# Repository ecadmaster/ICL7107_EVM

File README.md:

# ICL7107 Evaluation Module (EVM)

Este repositorio contiene el diseño de hardware de una tarjeta de evaluación para el ICL7107, un convertidor analógico-digital (ADC) de 3.5 dígitos diseñado para controlar displays LED. Este proyecto se desarrolla como material de práctica para la asignatura Laboratorio de Electrónica II de la Universidad de Los Andes (ULA).

## Descripción del Proyecto

El ICL7107 es un circuito integrado ampliamente utilizado en la instrumentación electrónica, específicamente en la construcción de voltímetros y multímetros digitales. Esta placa permite a los estudiantes y entusiastas experimentar con el acondicionamiento de señales y la visualización de datos sin necesidad de realizar el cableado complejo en protoboard.

## Características Técnicas

- Conversor: ICL7107 (ADC Dual-Slope).
- Visualización: 3.5 dígitos para displays de siete segmentos (ánodo común).
- Alimentación: $$+5VDC$$ vía microUSB, internamente contiene circuito inversor para el $$-5VDC$$.
- Ajustes: Potenciómetro de precisión para calibración de voltaje de referencia.
- Software de Diseño: [KiCad EDA](https://www.kicad.org/)  9.0 (o superior).

## Esquema del Circuito

A continuación, se presenta el diagrama esquemático del sistema:

## Lista de Materiales (BOM)

Para ensamblar este módulo, se requieren los siguientes componentes:

| Cantidad | Referencia | Descripción |
| :----------- | :-------------- | :------------- |
| 1	| C1 | Capacitor Electrolítico 47uF/16V |
| 5	| C2-6 | Capacitor Electrolítico 1uF/25V |
| 1	| C7 | Capacitor Cerámico 0.47uF |
| 1	| C8 | Capacitor Cerámico 0.22uF |
| 7	| C9-15 | Capacitor Cerámico 0.1uF |
| 1	| C16 | Capacitor Cerámico 0.047uF |
| 1	| C17 | Capacitor Cerámico 100pF |
| 4	| D1-4 | Display 7 segmentos, ánodo común |
| 1	| D5 | Diodo Zener 2.4V |
| 1	| J1 | Bornera 2 pines |
| 1	| JP1-6 | 1x02 Pin header con jumpers |
| 1	| P1 | Conector microUSB |
| 1	| R1 | Resistencia 1/4W 1 M ohm |
| 1	| R2 | Resistencia 1/4W 470k ohm |
| 1	| R3 | Resistencia 1/4W 100k ohm |
| 1	| R4 | Resistencia 1/4W 47k ohm |
| 1	| R5 | Resistencia 1/4W 10k ohm |
| 4	| R6-9 | Resistencia 1/4W 330 ohm |
| 1	| RV1 | Potenciómetro Trimmer 1k ohm |
| 1	| SW1 | Pulsador 6mm |
| 3	| SW2-4 | Switch, CuK OS102011MA1QN1 o similar |
| 1	| TP1-2 | Punta de prueba, Keystone 5010 o similar |
| 1	| U1 | Base de 40 pines + ICL7107 |
| 1	| U2 | Base de 16 pines + MAX232 |
| 1	| U3 | Regulador LM7905 |

Nota 1: La lista completa detallada se encuentra en el archivo ICL7107_EVM_BOM.csv

Nota 2: Se recomienda colocar 8x sockets de 1x05 pines hembra para la instalación de los display 7-segmento, de modo que pueda removerlos fácilmente de ser necesario.

## Instalación y Uso

Clona el repositorio:

```git clone https://github.com/ecadmaster/ICL7107_EVM.git```

Abre el archivo .kicad_pro con KiCad para revisar el PCB o generar los archivos Gerber para fabricación.

Consulta la datasheet para entender los límites operativos del integrado.

## Contribuciones y Licencia
Este proyecto está bajo la licencia MIT. Las sugerencias de mejora para el entorno académico de la Escuela de Ingeniería Eléctrica son bienvenidas.

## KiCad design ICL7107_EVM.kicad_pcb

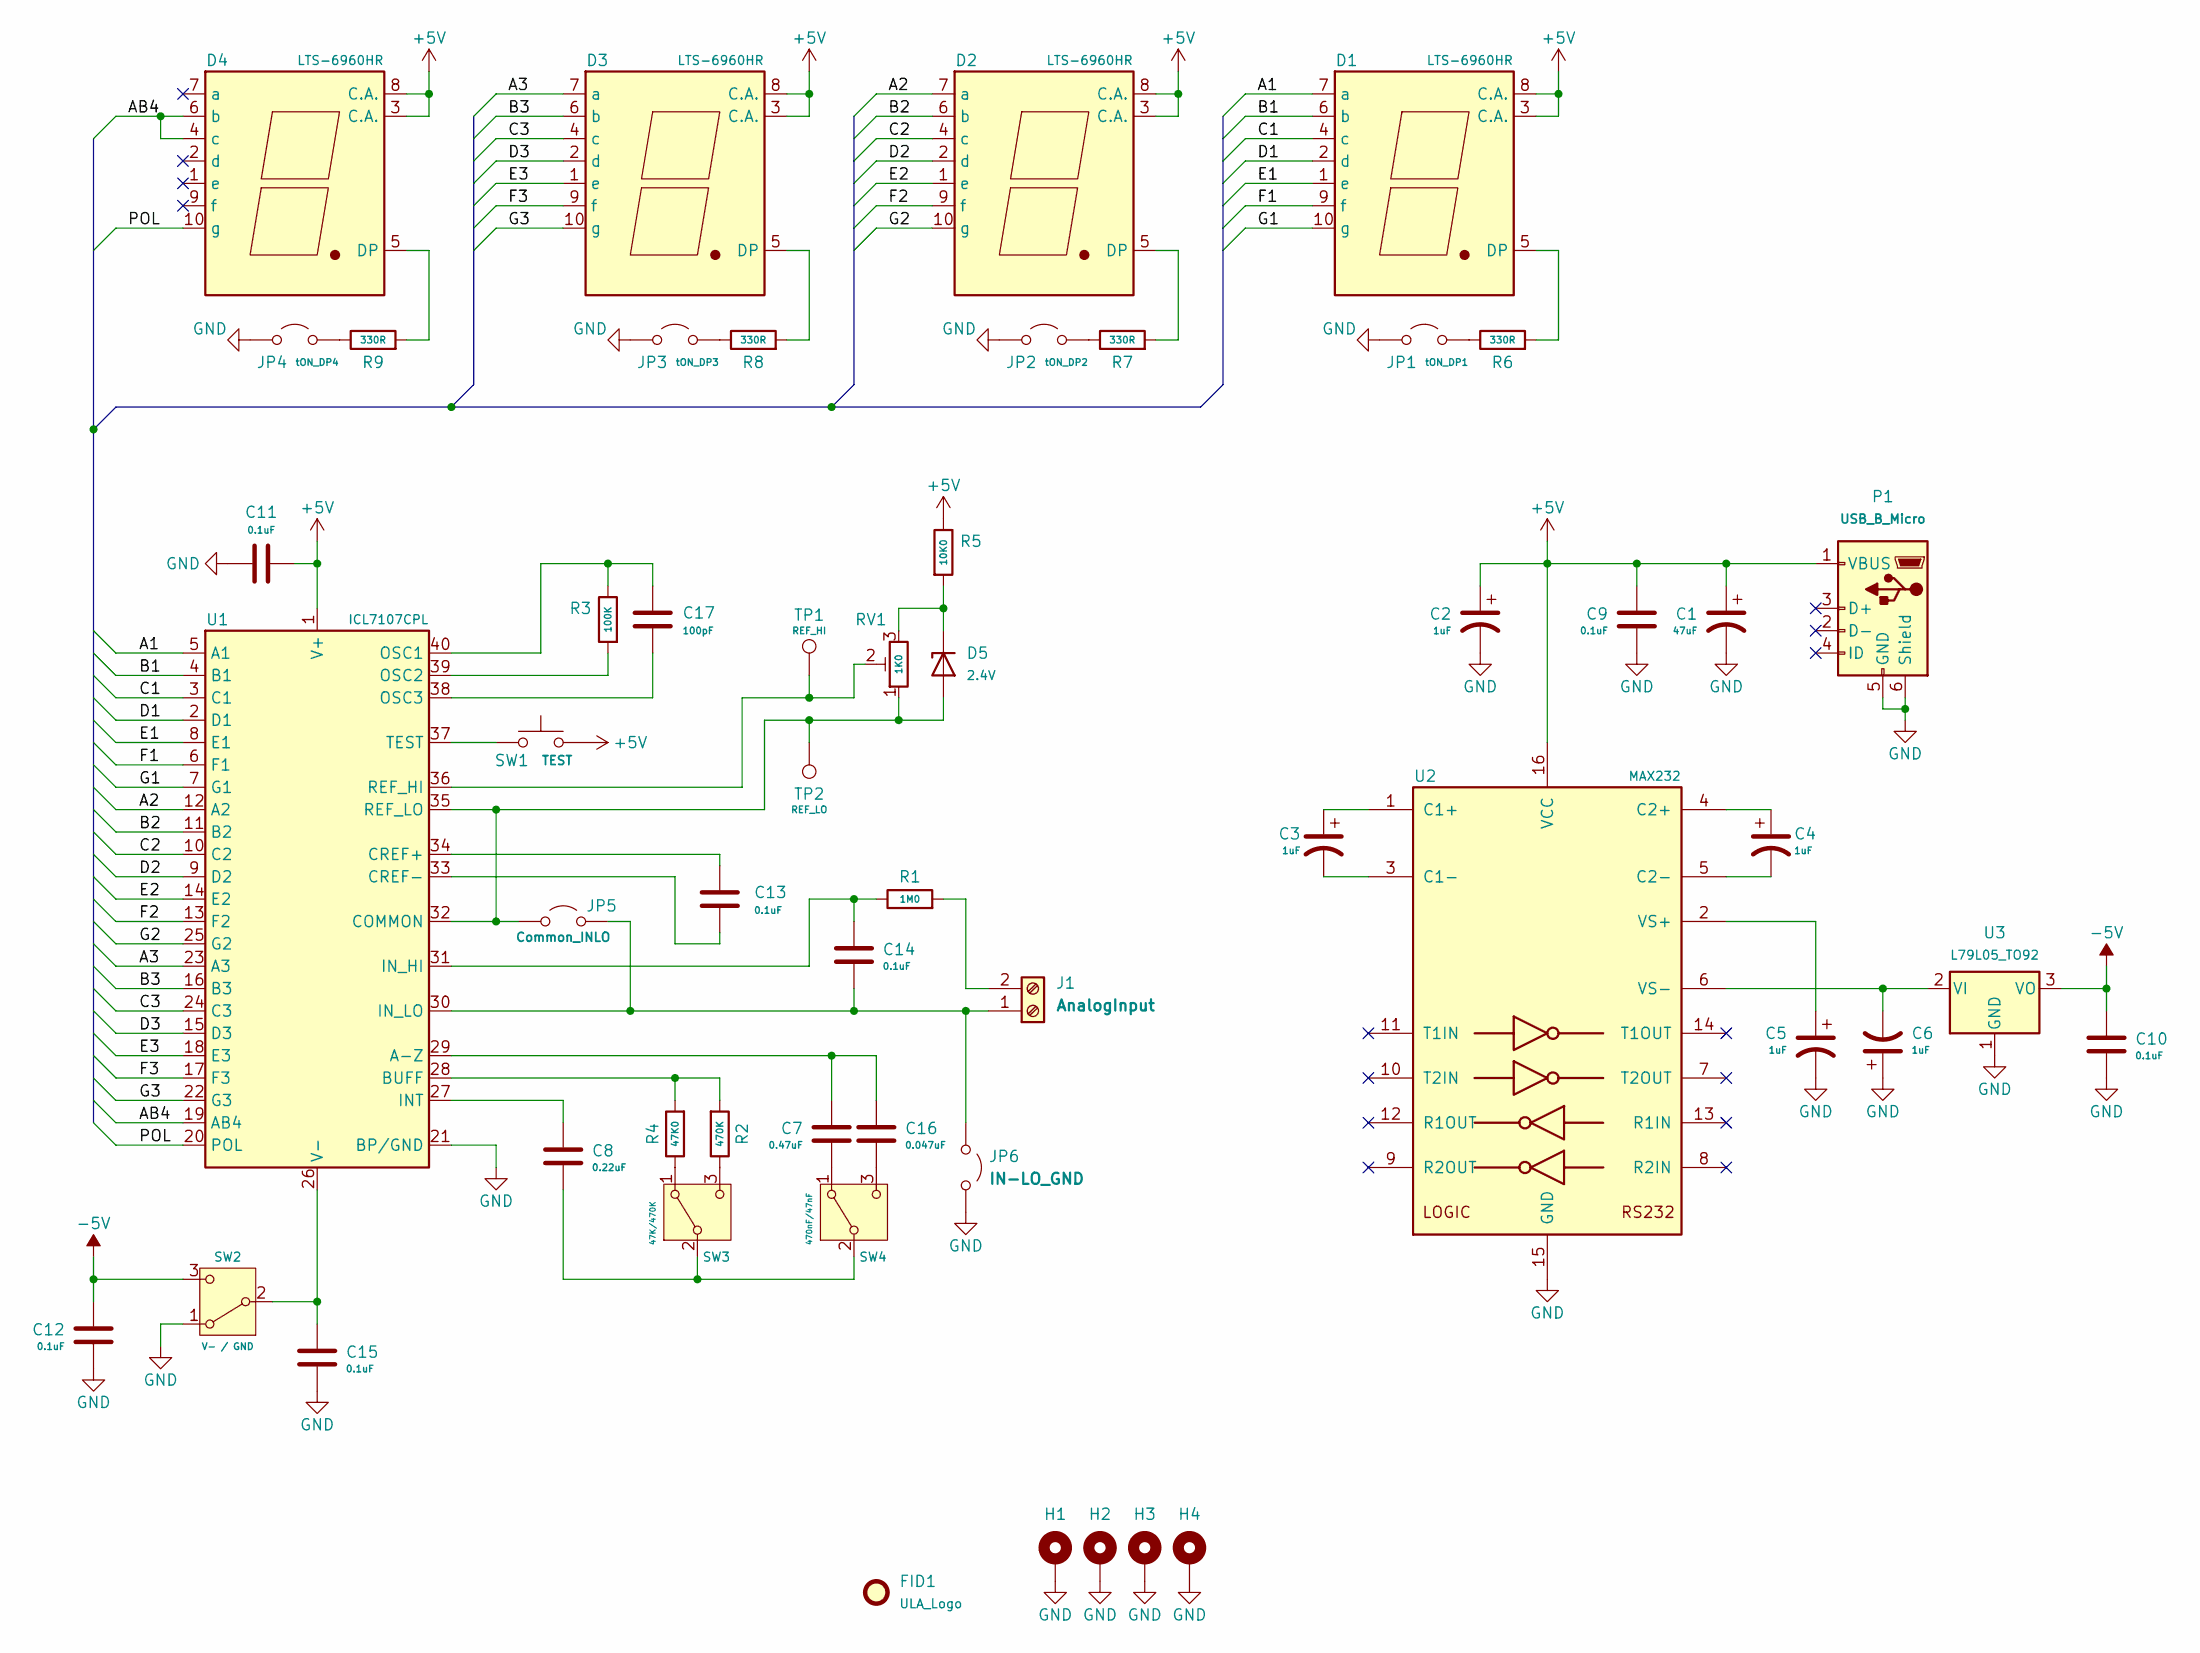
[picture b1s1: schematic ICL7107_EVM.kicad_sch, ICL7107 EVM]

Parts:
C1: 47uF; CP_Radial_D6.3mm_P2.50mm
C2, C3, C4, C5, C6: 1uF; CP_Radial_D5.0mm_P2.50mm
C7: 0.47uF; C_Disc_D4.7mm_W2.5mm_P5.00mm
C8: 0.22uF; C_Disc_D4.7mm_W2.5mm_P5.00mm
C9, C10, C11, C12, C13, C14, C15: 0.1uF; C_Disc_D4.7mm_W2.5mm_P5.00mm
C16: 0.047uF; C_Disc_D4.7mm_W2.5mm_P5.00mm
C17: 100pF; C_Disc_D4.7mm_W2.5mm_P5.00mm
D1, D2, D3, D4: LTS-6960HR; 7SegmentLED_LTS6760_LTS6780
D5: 2.4V; D_DO-35_SOD27_P7.62mm_Horizontal
FID1: ULA_Logo; ULA-Logo_9x12mm_SilkS
H1, H2, H3, H4: MountingHole_Pad; MountingHole_3.2mm_M3_Pad_Via
J1: AnalogInput; TerminalBlock_Phoenix_MKDS-1,5-2-5.08_1x02_P5.08mm_Horizont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
JP1: tON_DP1; PinHeader_1x02_P2.54mm_Vertical
JP2: tON_DP2; PinHeader_1x02_P2.54mm_Vertical
JP3: tON_DP3; PinHeader_1x02_P2.54mm_Vertical
JP4: tON_DP4; PinHeader_1x02_P2.54mm_Vertical
JP5: Common_INLO; PinHeader_1x02_P2.54mm_Vertical
JP6: IN-LO_GND; PinHeader_1x02_P2.54mm_Vertical
P1: USB_B_Micro; USB_Micro-B_Molex_47346-0001
R1: 1M0; R_Axial_DIN0204_L3.6mm_D1.6mm_P7.62mm_Horizontal
R2: 470K; R_Axial_DIN0204_L3.6mm_D1.6mm_P7.62mm_Horizontal
R3: 100K; R_Axial_DIN0204_L3.6mm_D1.6mm_P7.62mm_Horizontal
R4: 47K0; R_Axial_DIN0204_L3.6mm_D1.6mm_P7.62mm_Horizontal
R5: 10K0; R_Axial_DIN0204_L3.6mm_D1.6mm_P7.62mm_Horizontal
R6, R7, R8, R9: 330R; R_Axial_DIN0204_L3.6mm_D1.6mm_P7.62mm_Horizontal
RV1: 1K0; Potentiometer_Bourns_3299W_Vertical
SW1: TEST; SW_PUSH_6mm
SW2: V- / GND; SW_Slide_SPDT_Angled_CK_OS102011MA1Q
SW3: 47K/470K; SW_Slide_SPDT_Angled_CK_OS102011MA1Q
SW4: 470nF/47nF; SW_Slide_SPDT_Angled_CK_OS102011MA1Q
TP1: REF_HI; TestPoint_Keystone_5005-5009_Compact
TP2: REF_LO; TestPoint_Keystone_5005-5009_Compact
U1: ICL7107CPL; DIP-40_W15.24mm_Socket_LongPads
U2: MAX232; DIP-16_W7.62mm_Socket_LongPads
U3: L79L05_TO92; TO-92

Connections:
+5V: C1.1, C2.1, C9.1, C11.1, D1.3 (C.A.), D1.8 (C.A.), D2.3 (C.A.), D2.8 (C.A.), D3.3 (C.A.), D3.8 (C.A.), D4.3 (C.A.), D4.8 (C.A.), P1.1 (VBUS), R5.1, SW1.2, U1.1 (V+), U2.16 (VCC)
-5V: C10.1, C12.1, SW2.3 (C), U3.3 (VO)
/A1: D1.7 (a), U1.5 (A1)
/A2: D2.7 (a), U1.12 (A2)
/A3: D3.7 (a), U1.23 (A3)
/AB4: D4.4 (c), D4.6 (b), U1.19 (AB4)
/B1: D1.6 (b), U1.4 (B1)
/B2: D2.6 (b), U1.11 (B2)
/B3: D3.6 (b), U1.16 (B3)
/C1: D1.4 (c), U1.3 (C1)
/C2: D2.4 (c), U1.10 (C2)
/C3: D3.4 (c), U1.24 (C3)
/D1: D1.2 (d), U1.2 (D1)
/D2: D2.2 (d), U1.9 (D2)
/D3: D3.2 (d), U1.15 (D3)
/E1: D1.1 (e), U1.8 (E1)
/E2: D2.1 (e), U1.14 (E2)
/E3: D3.1 (e), U1.18 (E3)
/F1: D1.9 (f), U1.6 (F1)
/F2: D2.9 (f), U1.13 (F2)
/F3: D3.9 (f), U1.17 (F3)
/G1: D1.10 (g), U1.7 (G1)
/G2: D2.10 (g), U1.25 (G2)
/G3: D3.10 (g), U1.22 (G3)
/POL: D4.10 (g), U1.20 (POL)
GND: C1.2, C2.2, C5.2, C6.1, C9.2, C10.2, C11.2, C12.2, C15.2, H1.1, H2.1, H3.1, H4.1, JP1.1 (A), JP2.1 (A), JP3.1 (A), JP4.1 (A), JP6.2 (B), P1.5 (GND), P1.6 (Shield), SW2.1 (A), U1.21 (BP/GND), U2.15 (GND), U3.1 (GND)
unnamed: D1.5 (DP), R6.2
unnamed: D2.5 (DP), R7.2
unnamed: D3.5 (DP), R8.2
unnamed: D4.5 (DP), R9.2
unnamed: D5.2 (A), JP5.2 (B), RV1.1, TP2.1, U1.32 (COMMON), U1.35 (REF_LO)
unnamed: D5.1 (K), R5.2, RV1.3
unnamed: C14.2, J1.1, JP5.1 (A), JP6.1 (A), U1.30 (IN_LO)
unnamed: J1.2, R1.2
unnamed: JP1.2 (B), R6.1
unnamed: JP2.2 (B), R7.1
unnamed: JP3.2 (B), R8.1
unnamed: JP4.2 (B), R9.1
unnamed: C15.1, SW2.2 (B), U1.26 (V-)
unnamed: R4.1, SW3.1 (A)
unnamed: C8.2, SW3.2 (B), SW4.2 (B)
unnamed: R2.1, SW3.3 (C)
unnamed: C7.2, SW4.1 (A)
unnamed: C16.2, SW4.3 (C)
unnamed: C7.1, C16.1, U1.29 (A-Z)
unnamed: R2.2, R4.2, U1.28 (BUFF)
unnamed: C13.1, U1.34 (CREF+)
unnamed: C13.2, U1.33 (CREF-)
unnamed: C8.1, U1.27 (INT)
unnamed: C14.1, R1.1, U1.31 (IN_HI)
unnamed: C17.2, R3.1, U1.40 (OSC1)
unnamed: R3.2, U1.39 (OSC2)
unnamed: C17.1, U1.38 (OSC3)
unnamed: RV1.2, TP1.1, U1.36 (REF_HI)
unnamed: SW1.1, U1.37 (TEST)
unnamed: C3.1, U2.1 (C1+)
unnamed: C3.2, U2.3 (C1-)
unnamed: C4.1, U2.4 (C2+)
unnamed: C4.2, U2.5 (C2-)
unnamed: C5.1, U2.2 (VS+)
unnamed: C6.2, U2.6 (VS-), U3.2 (VI)

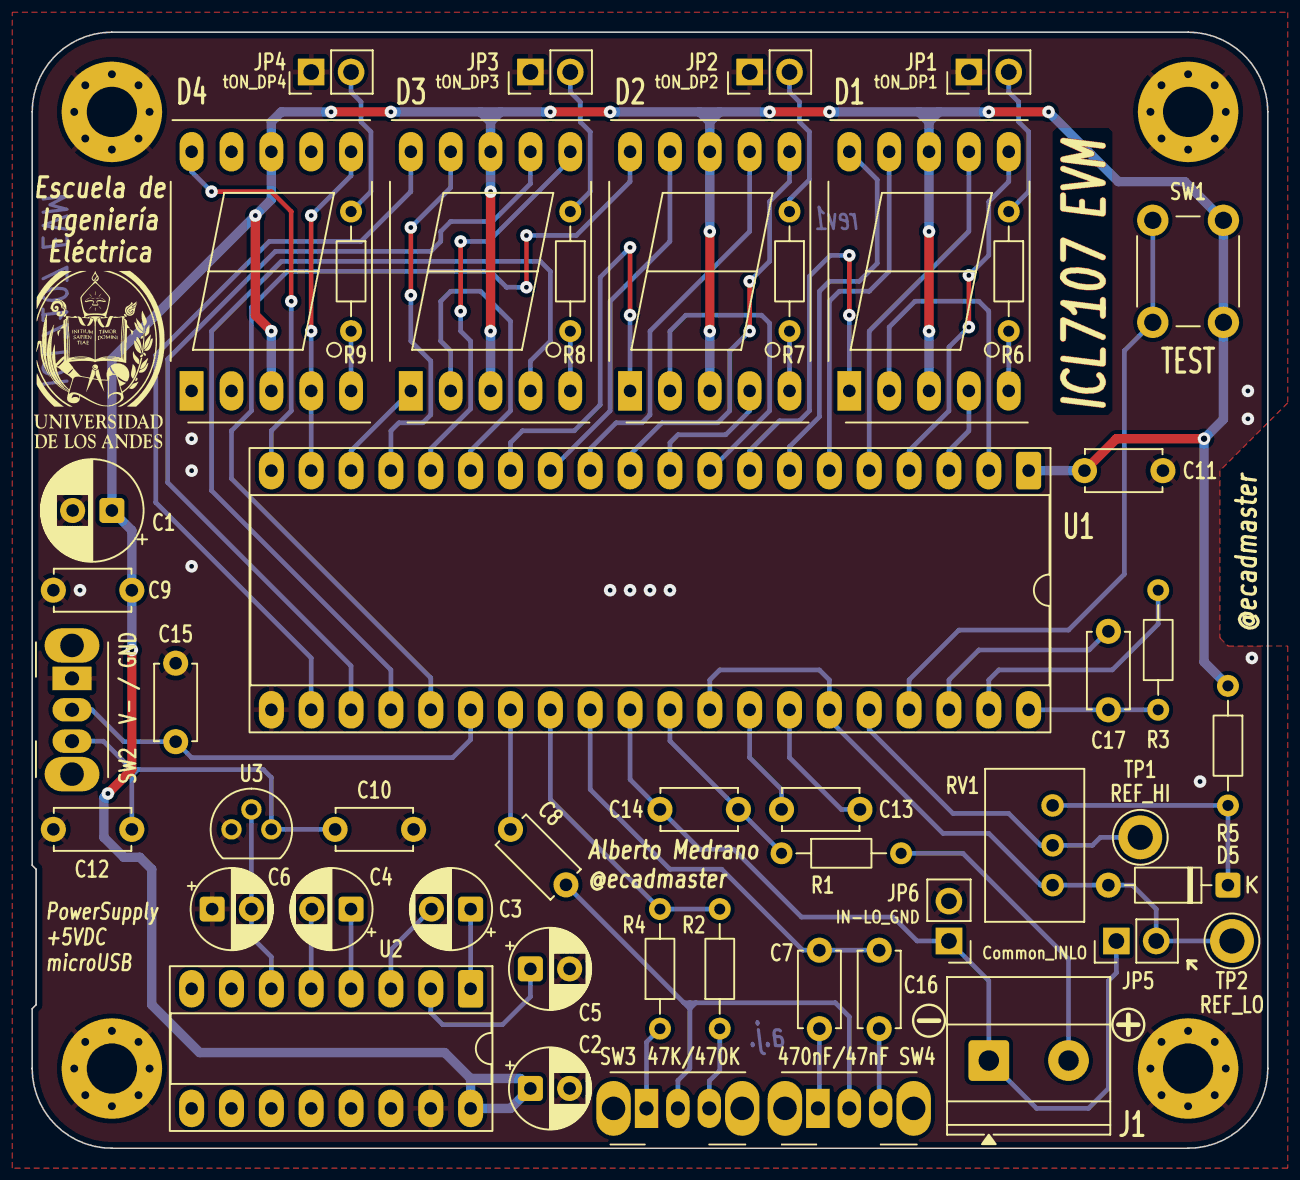
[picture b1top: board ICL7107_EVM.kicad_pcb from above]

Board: 2 copper layers, 78.7 x 71.1 mm, 54 parts (1 on the bottom side), 61 nets.

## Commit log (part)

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2026-04-20 agregando fuentes iniciales
2026-04-21 Update LICENSE

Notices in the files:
README.md:
License: MIT
